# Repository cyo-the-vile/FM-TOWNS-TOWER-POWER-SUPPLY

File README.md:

# FM-TOWNS-TOWER-POWER-SUPPLY
Replacement Power supply for FMT Tower units

This is a replacement for the aging FM Towns power supply.  It's a very well known fact in the niche FM Towns community that the power supply in the Tower models has chronic failure issues. This power supply revolves around using an ACDC converter with an ITX Pico PSU controlled by an Arduino Pro Micro.

This power supply can be used for the following FM Towns computers:

-MODEL 1
-MODEL 2
-SF
-SH
-1F
-2F
-1H
-2H
-10F
-20F
-40H
-80H
-CX10
-CX20
-CX40
-CX100
-SF2
-SH2

To assemble you need to program an Arduino Pro Micro in the Arduino IDE.  Once the Arduino is programmed solder the pin headers and Arduino to the PCB.

After that simply solder everything else.

The Arduino runs on the 5V Standby of the Pico PSU and controls the power on via original power button and also the TownsOS power off feature.

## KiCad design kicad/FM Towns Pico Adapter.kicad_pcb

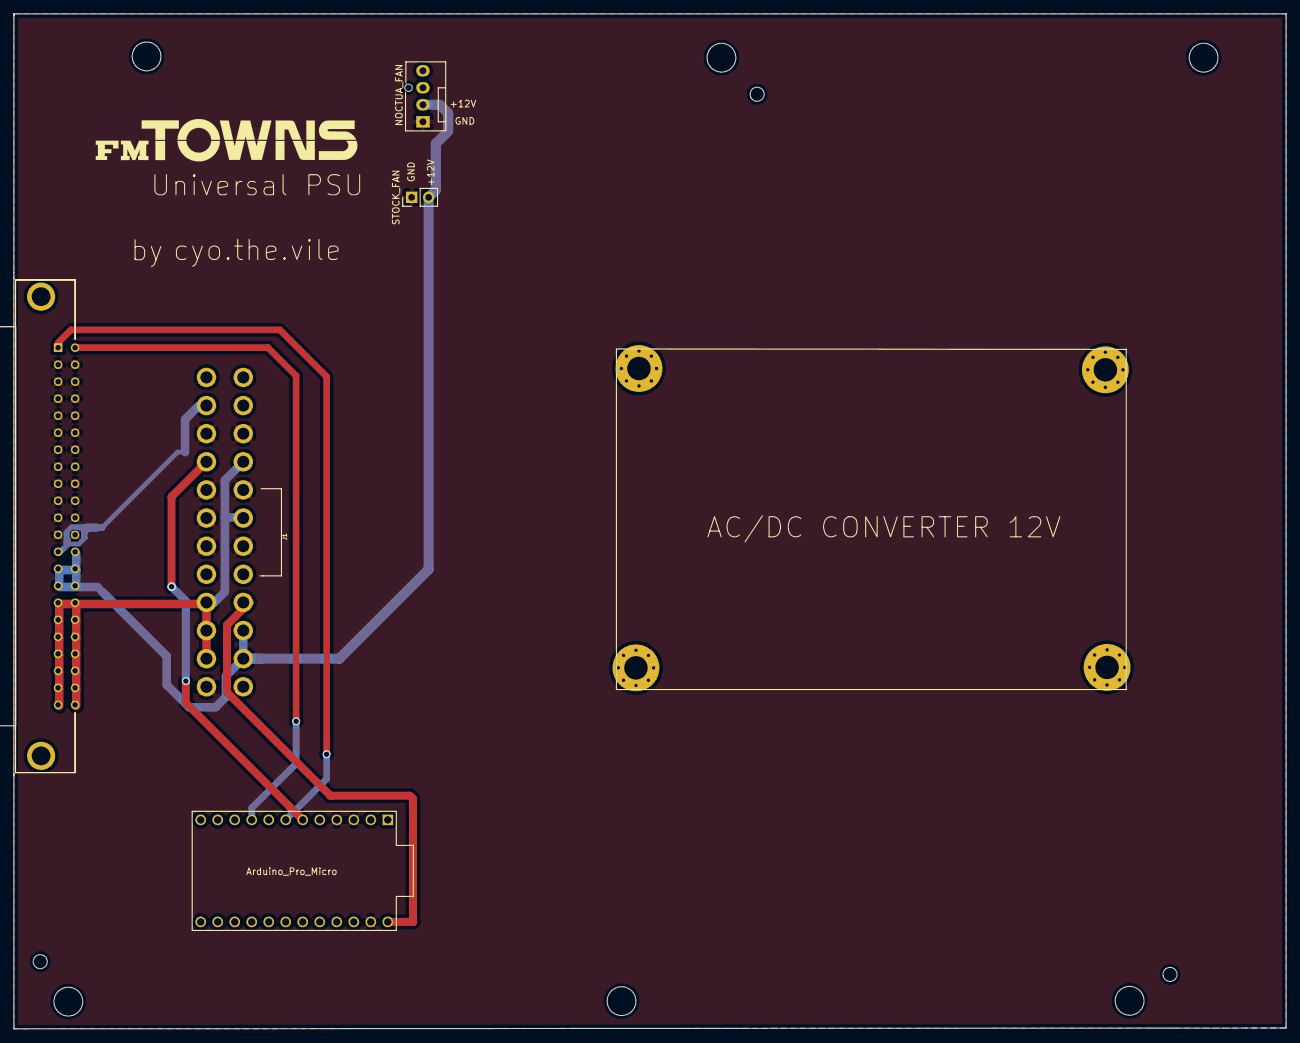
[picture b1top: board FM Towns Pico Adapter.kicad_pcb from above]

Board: 2 copper layers, 190.0 x 151.6 mm, 9 parts (0 on the bottom side), 8 nets.

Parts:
J1: ATX24RH; ATX24_RIGHT_ANGLE
J2: PCN13-44S-2.54DS_71_; PCN1344S254DS71
NOCTUA_FAN: 47053-1000; FanPinHeader_1x04_P2.54mm_Vertical
PAD1, PAD2, PAD3, PAD4: MountingHole_3.5mm_Pad_Via
STOCK_FAN: Conn_01x02; PinHeader_1x02_P2.54mm_Vertical
U1: ProMicro

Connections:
+5V: J1.4, J1.6, J1.21, J1.22, J1.23, J2.A16, J2.A17, J2.A18, J2.A19, J2.A20, J2.A21, J2.A22, J2.B16, J2.B17, J2.B18, J2.B19, J2.B20, J2.B21, J2.B22
+12V: J1.10, J1.11, J2.A14, J2.A15, J2.B13, J2.B14, J2.B15, NOCTUA_FAN.2, STOCK_FAN.2
-12V: J1.14, J2.A13
/5V_STBY: J1.9, U1.24
/FM_PS_OFF_N: J2.A1, U1.7
/FM_PS_ON_N: J2.B1, U1.9
/PS_ON: J1.16, U1.6
GND: J1.3, J1.5, J1.7, J1.15, J1.17, J1.18, J1.19, J1.24, J2.A2, J2.A3, J2.A4, J2.A5, J2.A6, J2.A7, J2.A8, J2.A9, J2.A10, J2.A11, J2.A12, J2.B2, J2.B3, J2.B4, J2.B5, J2.B6, J2.B7, J2.B8, J2.B9, J2.B10, J2.B11, J2.B12, NOCTUA_FAN.1, STOCK_FAN.1, U1.3, U1.4, U1.23

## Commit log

2021-04-14 GERBERS
    Factory output files for PCB fabrication
2021-04-14 Kicad Files
    Kicad files for editing PCB
2021-04-14 Arduino Script
    Script to configure Arduino Nano
2021-04-14 BOM file
    Bill of materials
2021-04-14 Update BOM
